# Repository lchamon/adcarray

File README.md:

# ADCArray: A prototype microphone array for the BeagleBone Black

This repository contains a prototype ADC microphone array cape for the BBB based on the ADS131E08.

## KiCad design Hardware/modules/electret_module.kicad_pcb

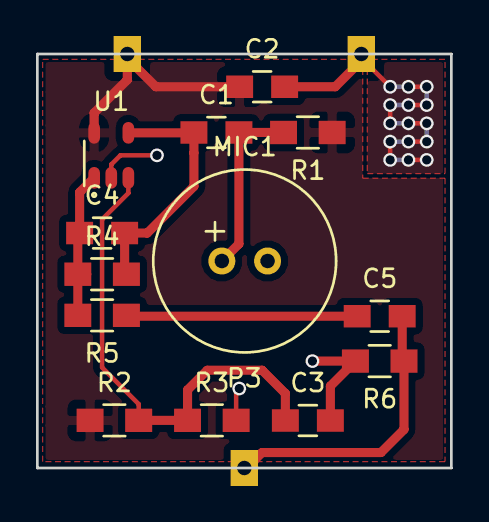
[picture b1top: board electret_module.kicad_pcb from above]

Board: 2 copper layers, 23.0 x 23.0 mm, 16 parts (0 on the bottom side), 8 nets.

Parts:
C1, C3, C5: 2.2u; C_0805_HandSoldering
C2: 100n; C_0805_HandSoldering
C4: 10p; C_0805_HandSoldering
MIC1: ELECTRET; Electret_10mm
P1, P2, P3: CONN_01X01; Castellated_Pad
R1: 13.7k; R_0805_HandSoldering
R2, R3, R6: 100k; R_0805_HandSoldering
R4: 75k; R_0805_HandSoldering
R5: 49.9; R_0805_HandSoldering
U1: OPA172; SOT-23-5

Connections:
/OUT: C5.2, P3.1, R6.1
AGND: C2.2, C3.2, MIC1.2, P2.1, R3.2, R6.2, U1.2
AVDD: C2.1, P1.1, R1.1, R2.1, U1.5
unnamed: C1.1, C4.2, R4.2, U1.4
unnamed: C1.2, MIC1.1, R1.2
unnamed: C3.1, R2.2, R3.1, U1.3
unnamed: C4.1, R4.1, R5.2, U1.1
unnamed: C5.1, R5.1

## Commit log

2015-12-18 First commit.
2015-12-22 Move designs to separate folders.
2015-12-22 Design electret microphone module and update footprints.
2015-12-22 Remove wrong component footprint.
2015-12-22 Copy schematic from ProtoArray (ULA).
2015-12-22 Add circuit reference.
2015-12-22 Add schematic for the ADC array.
2015-12-26 Redraw schematic with one hierarchy per ADC.
2015-12-26 Annotate schematics.
2016-02-21 Move hardware files to /Hardware folder.
2016-02-21 Add README.
